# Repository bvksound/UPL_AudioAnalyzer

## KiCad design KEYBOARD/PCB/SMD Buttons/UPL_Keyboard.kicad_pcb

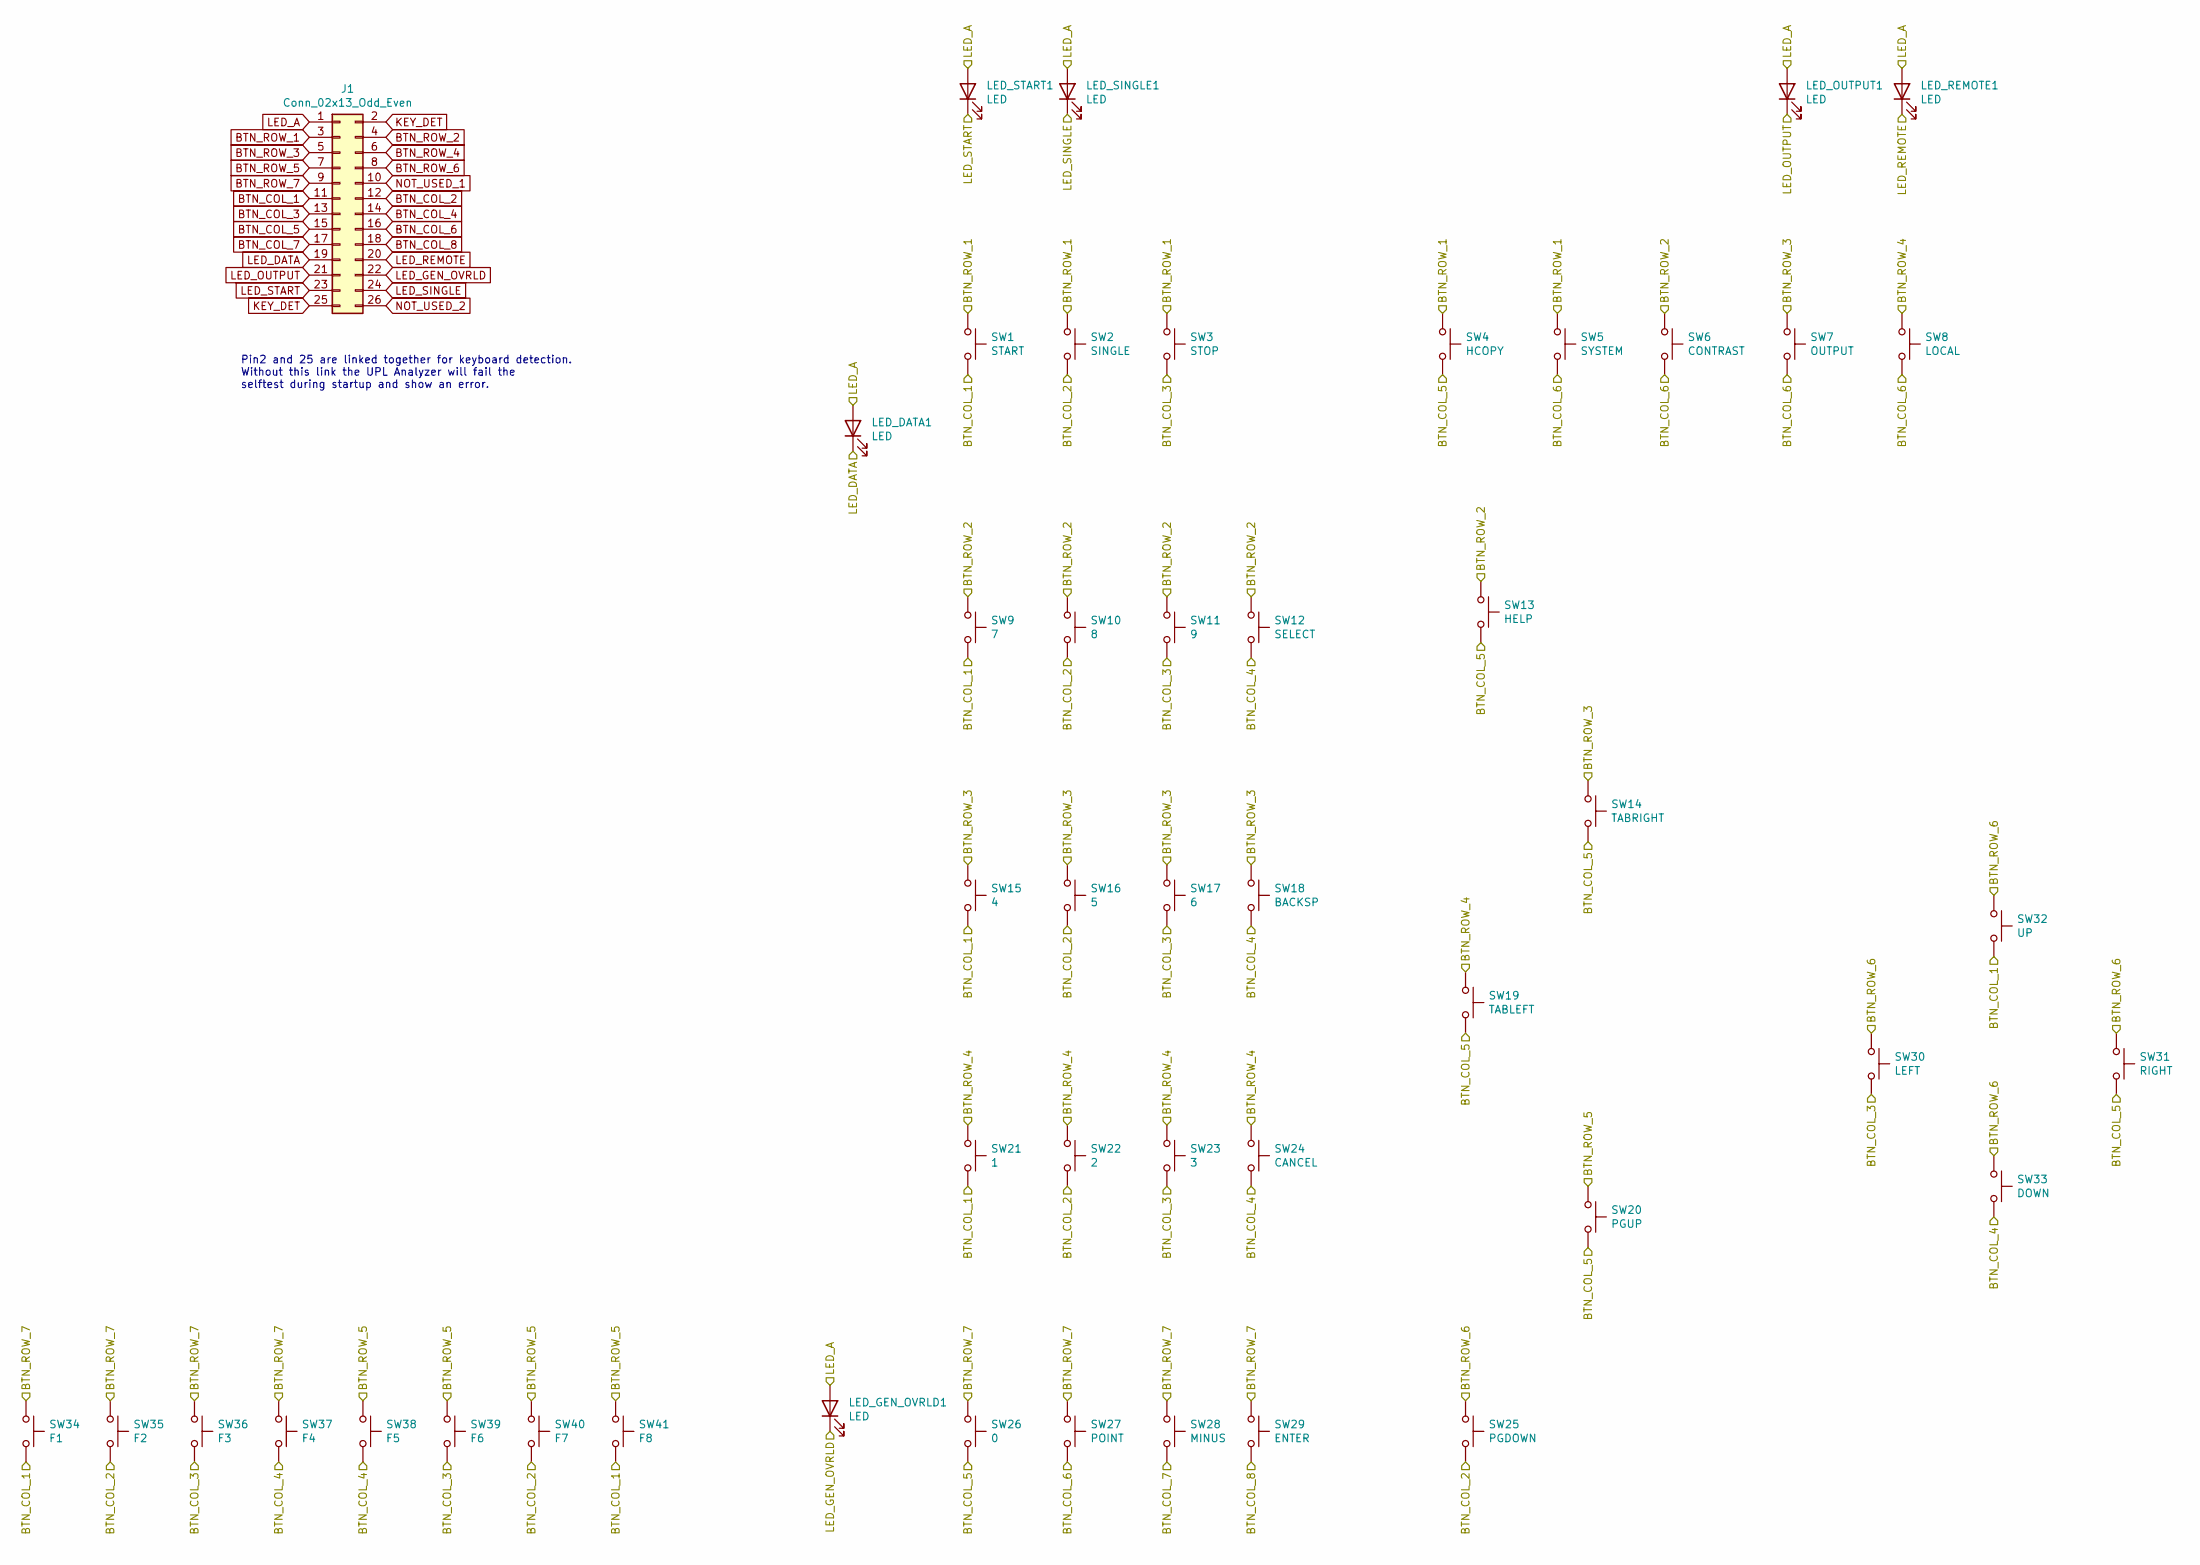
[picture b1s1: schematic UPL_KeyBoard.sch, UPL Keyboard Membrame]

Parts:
J1: Conn_02x13_Odd_Even; 0520443445_Mirrored
LED_DATA1: LED; LED_1206_3216Metric
LED_GEN_OVRLD1: LED; LED_1206_3216Metric
LED_OUTPUT1: LED; LED_1206_3216Metric
LED_REMOTE1: LED; LED_1206_3216Metric
LED_SINGLE1: LED; LED_1206_3216Metric
LED_START1: LED; LED_1206_3216Metric
SW1: START; EVQ-Q2B01W
SW2: SINGLE; EVQ-Q2B01W
SW3: STOP; EVQ-Q2B01W
SW4: HCOPY; EVQ-Q2B01W
SW5: SYSTEM; EVQ-Q2B01W
SW6: CONTRAST; EVQ-Q2B01W
SW7: OUTPUT; EVQ-Q2B01W
SW8: LOCAL; EVQ-Q2B01W
SW9: 7; EVQ-Q2B01W
SW10: 8; EVQ-Q2B01W
SW11: 9; EVQ-Q2B01W
SW12: SELECT; EVQ-Q2B01W
SW13: HELP; EVQ-Q2B01W
SW14: TABRIGHT; EVQ-Q2B01W
SW15: 4; EVQ-Q2B01W
SW16: 5; EVQ-Q2B01W
SW17: 6; EVQ-Q2B01W
SW18: BACKSP; EVQ-Q2B01W
SW19: TABLEFT; EVQ-Q2B01W
SW20: PGUP; EVQ-Q2B01W
SW21: 1; EVQ-Q2B01W
SW22: 2; EVQ-Q2B01W
SW23: 3; EVQ-Q2B01W
SW24: CANCEL; EVQ-Q2B01W
SW25: PGDOWN; EVQ-Q2B01W
SW26: 0; EVQ-Q2B01W
SW27: POINT; EVQ-Q2B01W
SW28: MINUS; EVQ-Q2B01W
SW29: ENTER; EVQ-Q2B01W
SW30: LEFT; EVQ-Q2B01W
SW31: RIGHT; EVQ-Q2B01W
SW32: UP; EVQ-Q2B01W
SW33: DOWN; EVQ-Q2B01W
SW34: F1; EVQ-Q2B01W
SW35: F2; EVQ-Q2B01W
SW36: F3; EVQ-Q2B01W
SW37: F4; EVQ-Q2B01W
SW38: F5; EVQ-Q2B01W
SW39: F6; EVQ-Q2B01W
SW40: F7; EVQ-Q2B01W
SW41: F8; EVQ-Q2B01W

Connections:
BTN_COL_1: J1.11, SW1.2, SW9.2, SW15.2, SW21.2, SW32.2, SW34.2, SW41.2
BTN_COL_2: J1.12, SW2.2, SW10.2, SW16.2, SW22.2, SW25.2, SW35.2, SW40.2
BTN_COL_3: J1.13, SW3.2, SW11.2, SW17.2, SW23.2, SW30.2, SW36.2, SW39.2
BTN_COL_4: J1.14, SW12.2, SW18.2, SW24.2, SW33.2, SW37.2, SW38.2
BTN_COL_5: J1.15, SW4.2, SW13.2, SW14.2, SW19.2, SW20.2, SW26.2, SW31.2
BTN_COL_6: J1.16, SW5.2, SW6.2, SW7.2, SW8.2, SW27.2
BTN_COL_7: J1.17, SW28.2
BTN_COL_8: J1.18, SW29.2
BTN_ROW_1: J1.3, SW1.1, SW2.1, SW3.1, SW4.1, SW5.1
BTN_ROW_2: J1.4, SW6.1, SW9.1, SW10.1, SW11.1, SW12.1, SW13.1
BTN_ROW_3: J1.5, SW7.1, SW14.1, SW15.1, SW16.1, SW17.1, SW18.1
BTN_ROW_4: J1.6, SW8.1, SW19.1, SW21.1, SW22.1, SW23.1, SW24.1
BTN_ROW_5: J1.7, SW20.1, SW38.1, SW39.1, SW40.1, SW41.1
BTN_ROW_6: J1.8, SW25.1, SW30.1, SW31.1, SW32.1, SW33.1
BTN_ROW_7: J1.9, SW26.1, SW27.1, SW28.1, SW29.1, SW34.1, SW35.1, SW36.1, SW37.1
KEY_DET: J1.2, J1.25
LED_A: J1.1, LED_DATA1.2 (A), LED_GEN_OVRLD1.2 (A), LED_OUTPUT1.2 (A), LED_REMOTE1.2 (A), LED_SINGLE1.2 (A), LED_START1.2 (A)
LED_DATA: J1.19, LED_DATA1.1 (K)
LED_GEN_OVRLD: J1.22, LED_GEN_OVRLD1.1 (K)
LED_OUTPUT: J1.21, LED_OUTPUT1.1 (K)
LED_REMOTE: J1.20, LED_REMOTE1.1 (K)
LED_SINGLE: J1.24, LED_SINGLE1.1 (K)
LED_START: J1.23, LED_START1.1 (K)
NOT_USED_1: J1.10
NOT_USED_2: J1.26

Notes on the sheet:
Pin2 and 25 are linked together for keyboard detection. Without this link the UPL Analyzer will fail the selftest during startup and show an error.

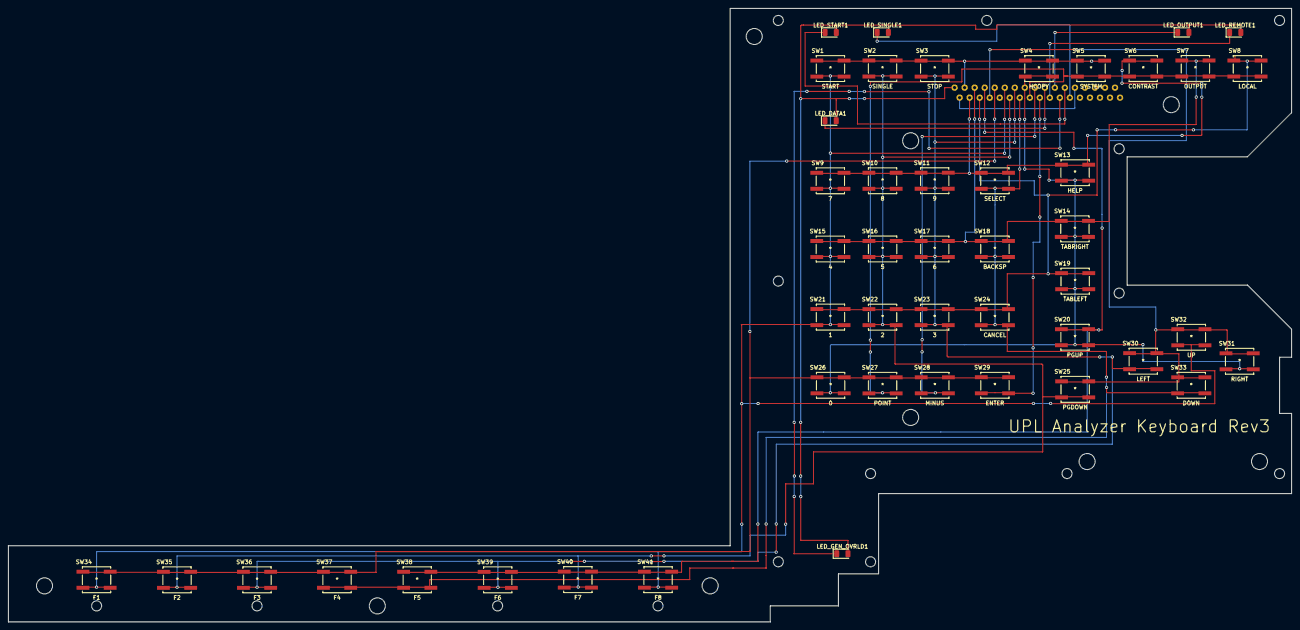
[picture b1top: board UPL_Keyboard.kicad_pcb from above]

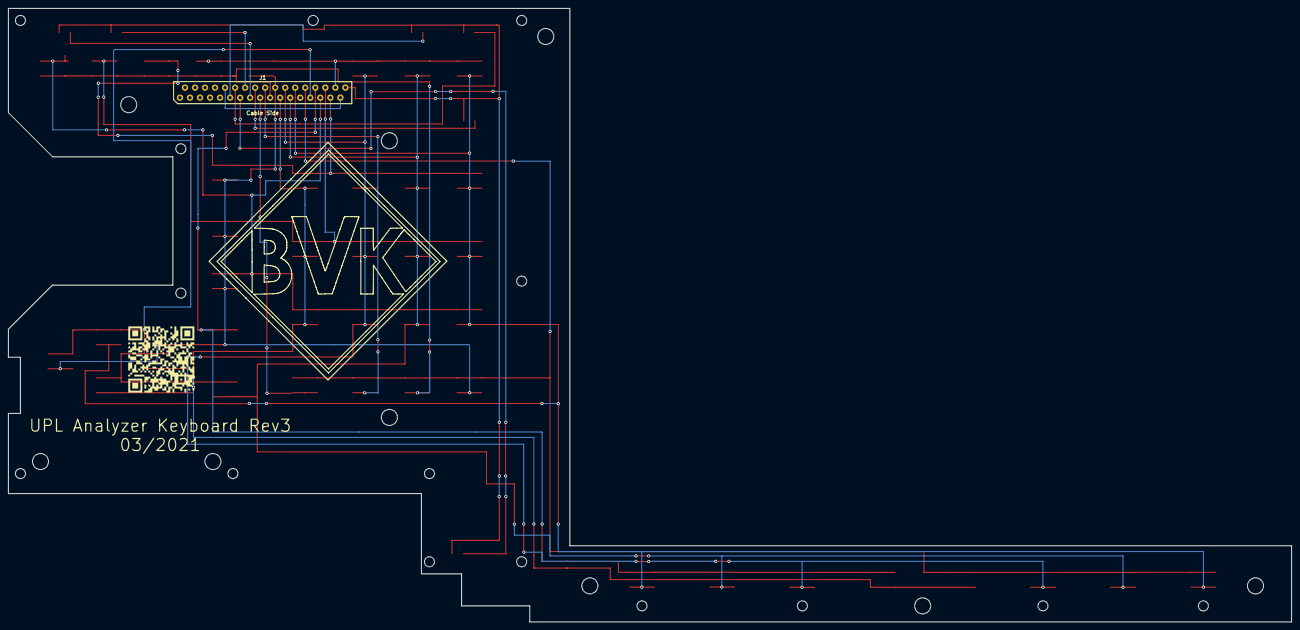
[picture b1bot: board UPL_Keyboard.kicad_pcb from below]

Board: 2 copper layers, 320.0 x 153.0 mm, 49 parts (2 on the bottom side), 23 nets.

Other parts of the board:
QR*****: www.bvksound.be

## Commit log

2020-04-14 Test Commit
2020-04-14 draft added
2020-04-19 Keyboard shortcuts added
2020-04-19 Updated design of fusion 360, also backupped in the cloud of autodesk
2020-04-19 schematic done
2020-04-20 first draft of pcb design, bom added, gerber configuration added
2020-04-20 final design added
2020-04-28 Removed trailing trace, final design, Freeze
2020-05-05 updated with remaining components
2020-05-09 basic program added
2020-11-25 add document
2021-01-23 ISA Board Added
    Reorganised + added first revision of ISA Interconnect board
2021-02-03 Membrame version draft schematic added
2021-02-13 Kicad Rev2
    Kicad design added based on new smaller ALPS buttons
2021-02-13 cleanup pcb
    cleanup move connector for more clearance screw
2021-03-18 Update of SMD button manufacturer
    Change SMD buttons to EVQQ2P02W
2021-03-20 Finalized design with FFC Connector
2021-03-26 final update rev3
2021-11-21 Rev3 updated Bom
    update outdated BOM

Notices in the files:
parts and their libraries:
Copyright 2016 Accelerated Designs. All rights reserved.
